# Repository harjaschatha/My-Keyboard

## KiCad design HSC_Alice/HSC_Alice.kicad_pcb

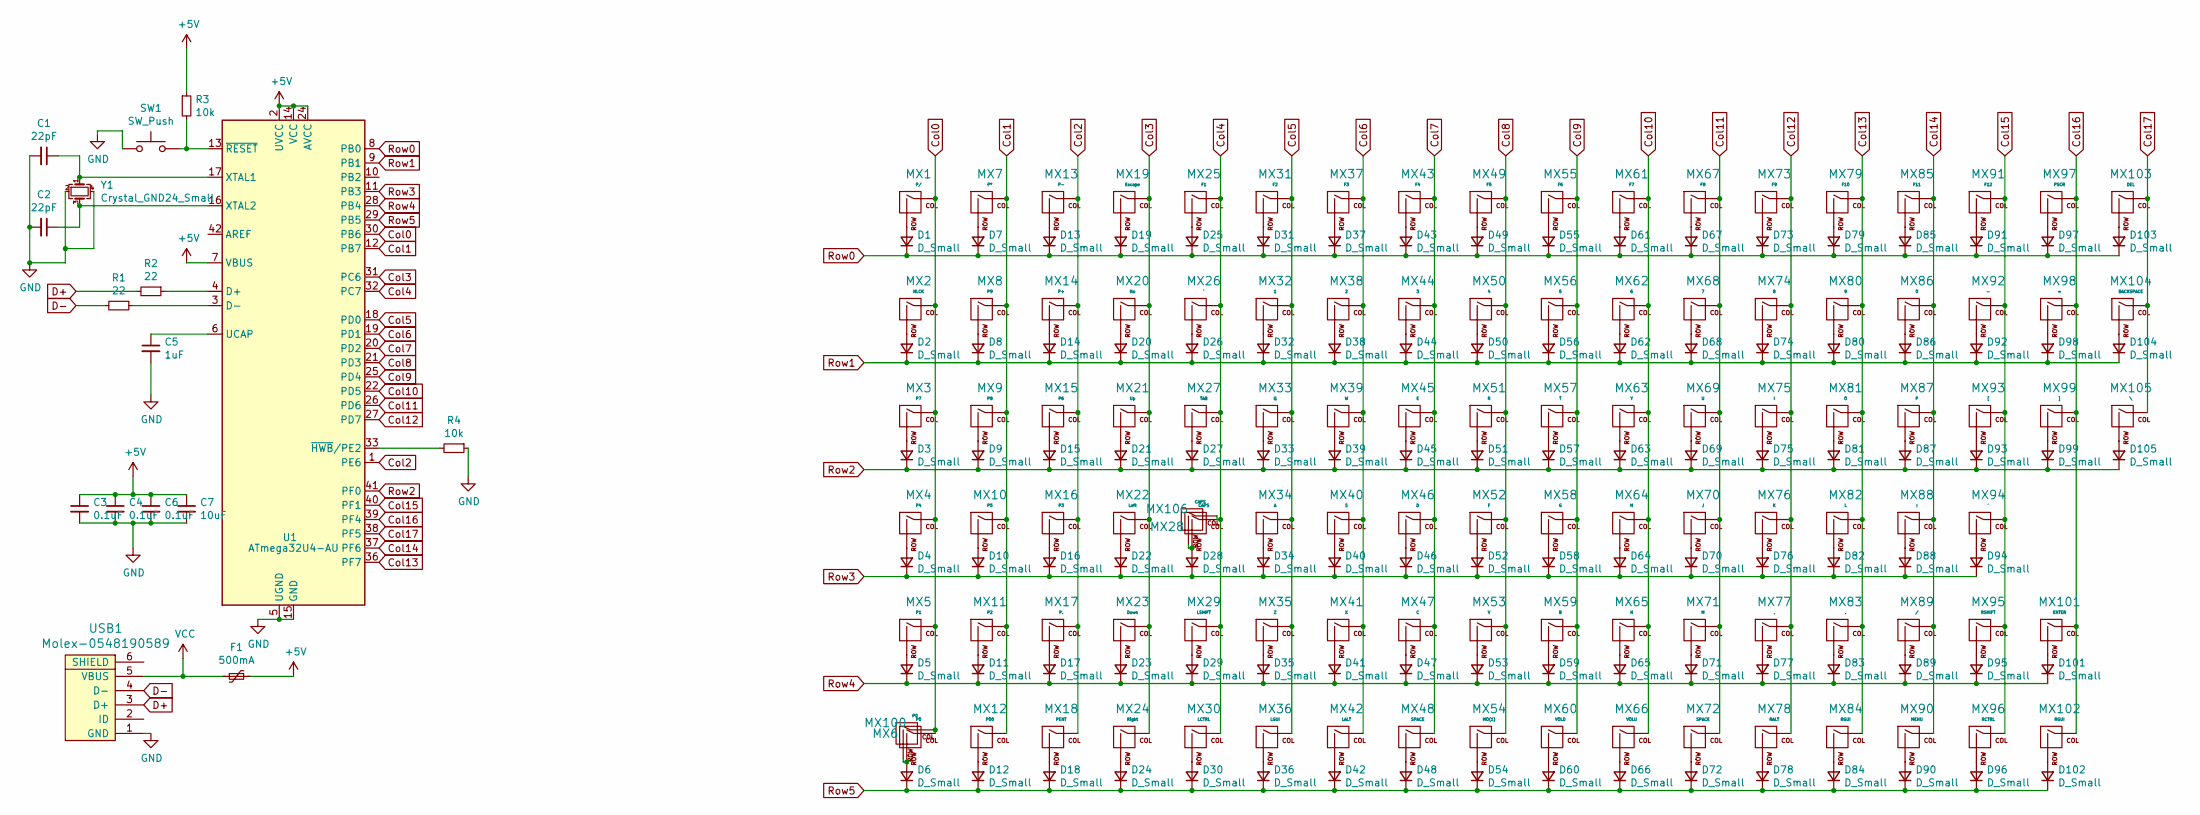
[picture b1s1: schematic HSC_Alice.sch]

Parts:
C1, C2: 22pF; C_0805_2012Metric
C3, C4, C6: 0.1uF; C_0805_2012Metric
C5: 1uF; C_0805_2012Metric
C7: 10uF; C_0805_2012Metric
D1, D2, D3, D4, D5, D6, D7, D8, D9, D10, D11, D12, D13, D14, D15, D16, D17, D18, D19, D20, D21, D22, D23, D24, D25, D26, D27, D28, D29, D30, D31, D32, D33, D34, D35, D36, D37, D38, D39, D40, D41, D42, D43, D44, D45, D46, D47, D48, D49, D50, D51, D52, D53, D54, D55, D56, D57, D58, D59, D60, D61, D62, D63, D64, D65, D66, D67, D68, D69, D70, D71, D72, D73, D74, D75, D76, D77, D78, D79, D80, D81, D82, D83, D84, D85, D86, D87, D88, D89, D90, D91, D92, D93, D94, D95, D96, D97, D98, D99, D101, D102, D103, D104, D105: D_Small; D_SOD-123
F1: 500mA; Fuse_1206_3216Metric
MX1: P/; MXOnly-1U-Hotswap
MX2: NLCK; MXOnly-1U-Hotswap
MX3: P7; MXOnly-1U-Hotswap
MX4: P4; MXOnly-1U-Hotswap
MX5: P1; MXOnly-1U-Hotswap
MX6: P0; MXOnly-1U-Hotswap
MX7: P*; MXOnly-1U-Hotswap
MX8: P9; MXOnly-1U-Hotswap
MX9: P8; MXOnly-1U-Hotswap
MX10: P5; MXOnly-1U-Hotswap
MX11: P2; MXOnly-1U-Hotswap
MX12: P00; MXOnly-1U-Hotswap
MX13: P-; MXOnly-1U-Hotswap
MX14: P+; MXOnly-2U-Hotswap
MX15: P6; MXOnly-1U-Hotswap
MX16: P3; MXOnly-1U-Hotswap
MX17: P.; MXOnly-1U-Hotswap
MX18: PENT; MXOnly-2U-Hotswap
MX19: Escape; MXOnly-1U-Hotswap
MX20: No; MXOnly-1U-Hotswap
MX21: Up; MXOnly-1U-Hotswap
MX22: Left; MXOnly-1U-Hotswap
MX23: Down; MXOnly-1U-Hotswap
MX24: Right; MXOnly-1U-Hotswap
MX25: F1; MXOnly-1U-Hotswap
MX26: `; MXOnly-1U-Hotswap
MX27: TAB; MXOnly-1.5U-Hotswap
MX28: CAPS; MXOnly-1.75U-Hotswap
MX29: LSHIFT; MXOnly-2.25U-Hotswap
MX30: LCTRL; MXOnly-1.25U-Hotswap
MX31: F2; MXOnly-1U-Hotswap
MX32: 1; MXOnly-1U-Hotswap
MX33: Q; MXOnly-1U-Hotswap
MX34: A; MXOnly-1U-Hotswap
MX35: Z; MXOnly-1U-Hotswap
MX36: LGUI; MXOnly-1.25U-Hotswap
MX37: F3; MXOnly-1U-Hotswap
MX38: 2; MXOnly-1U-Hotswap
MX39: W; MXOnly-1U-Hotswap
MX40: S; MXOnly-1U-Hotswap
MX41: X; MXOnly-1U-Hotswap
MX42: LALT; MXOnly-1.25U-Hotswap
MX43: F4; MXOnly-1U-Hotswap
MX44: 3; MXOnly-1U-Hotswap
MX45: E; MXOnly-1U-Hotswap
MX46: D; MXOnly-1U-Hotswap
MX47: C; MXOnly-1U-Hotswap
MX48, MX72: SPACE; MXOnly-2.75U-Hotswap-ReversedStabilizers
MX49: F5; MXOnly-1U-Hotswap
MX50: 4; MXOnly-1U-Hotswap
MX51: R; MXOnly-1U-Hotswap
MX52: F; MXOnly-1U-Hotswap
MX53: V; MXOnly-1U-Hotswap
MX54: MO(1); MXOnly-1U-Hotswap
MX55: F6; MXOnly-1U-Hotswap
MX56: 5; MXOnly-1U-Hotswap
MX57: T; MXOnly-1U-Hotswap
MX58: G; MXOnly-1U-Hotswap
MX59: B; MXOnly-1U-Hotswap
MX60: VOLD; MXOnly-1U-Hotswap
MX61: F7; MXOnly-1U-Hotswap
MX62: 6; MXOnly-1U-Hotswap
MX63: Y; MXOnly-1U-Hotswap
MX64: H; MXOnly-1U-Hotswap
MX65: N; MXOnly-1U-Hotswap
MX66: VOLU; MXOnly-1U-Hotswap
MX67: F8; MXOnly-1U-Hotswap
MX68: 7; MXOnly-1U-Hotswap
MX69: U; MXOnly-1U-Hotswap
MX70: J; MXOnly-1U-Hotswap
MX71: M; MXOnly-1U-Hotswap
MX73: F9; MXOnly-1U-Hotswap
MX74: 8; MXOnly-1U-Hotswap
MX75: I; MXOnly-1U-Hotswap
MX76: K; MXOnly-1U-Hotswap
MX77: ,; MXOnly-1U-Hotswap
MX78: RALT; MXOnly-1.25U-Hotswap
MX79: F10; MXOnly-1U-Hotswap
MX80: 9; MXOnly-1U-Hotswap
MX81: O; MXOnly-1U-Hotswap
MX82: L; MXOnly-1U-Hotswap
MX83: .; MXOnly-1U-Hotswap
MX84: RGUI; MXOnly-1.25U-Hotswap
MX85: F11; MXOnly-1U-Hotswap
MX86: 0; MXOnly-1U-Hotswap
MX87: P; MXOnly-1U-Hotswap
MX88: ;; MXOnly-1U-Hotswap
MX89: /; MXOnly-1U-Hotswap
MX90: MENU; MXOnly-1.25U-Hotswap
MX91: F12; MXOnly-1U-Hotswap
MX92: -; MXOnly-1U-Hotswap
MX93: [; MXOnly-1U-Hotswap
MX94: '; MXOnly-1U-Hotswap
MX95: RSHIFT; MXOnly-2.25U-Hotswap
MX96: RCTRL; MXOnly-1.25U-Hotswap
MX97: PSCR; MXOnly-1U-Hotswap
MX98: =; MXOnly-1U-Hotswap
MX99: ]; MXOnly-1U-Hotswap
MX100: P0; MXOnly-2U-Hotswap-ReversedStabilizers
MX101: ENTER; MXOnly-2.25U-Hotswap
MX102: RGUI; MXOnly-1U-Hotswap
MX103: DEL; MXOnly-1U-Hotswap
MX104: BACKSPACE; MXOnly-2U-Hotswap
MX105: \\; MXOnly-1.5U-Hotswap
MX106: CAPS; MXOnly-1.25U-Hotswap
R1, R2: 22; R_0805_2012Metric
R3, R4: 10k; R_0805_2012Metric
SW1: SW_Push; SKQG-1155865
U1: ATmega32U4-AU; TQFP-44_10x10mm_P0.8mm
USB1: Molex-0548190589
Y1: Crystal_GND24_Small; Crystal_SMD_3225-4Pin_3.2x2.5mm

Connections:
+5V: C3.1, C4.1, C6.1, C7.1, F1.1, R3.1, U1.2 (UVCC), U1.7 (VBUS), U1.14 (VCC), U1.24 (AVCC), U1.34 (VCC), U1.44 (AVCC)
Col0: MX1.1 (COL), MX2.1 (COL), MX3.1 (COL), MX4.1 (COL), MX5.1 (COL), MX6.1 (COL), MX100.1 (COL), U1.30 (PB6)
Col1: MX7.1 (COL), MX8.1 (COL), MX9.1 (COL), MX10.1 (COL), MX11.1 (COL), MX12.1 (COL), U1.12 (PB7)
Col2: MX13.1 (COL), MX14.1 (COL), MX15.1 (COL), MX16.1 (COL), MX17.1 (COL), MX18.1 (COL), U1.1 (PE6)
Col3: MX19.1 (COL), MX20.1 (COL), MX21.1 (COL), MX22.1 (COL), MX23.1 (COL), MX24.1 (COL), U1.31 (PC6)
Col4: MX25.1 (COL), MX26.1 (COL), MX27.1 (COL), MX28.1 (COL), MX29.1 (COL), MX30.1 (COL), MX106.1 (COL), U1.32 (PC7)
Col5: MX31.1 (COL), MX32.1 (COL), MX33.1 (COL), MX34.1 (COL), MX35.1 (COL), MX36.1 (COL), U1.18 (PD0)
Col6: MX37.1 (COL), MX38.1 (COL), MX39.1 (COL), MX40.1 (COL), MX41.1 (COL), MX42.1 (COL), U1.19 (PD1)
Col7: MX43.1 (COL), MX44.1 (COL), MX45.1 (COL), MX46.1 (COL), MX47.1 (COL), MX48.1 (COL), U1.20 (PD2)
Col8: MX49.1 (COL), MX50.1 (COL), MX51.1 (COL), MX52.1 (COL), MX53.1 (COL), MX54.1 (COL), U1.21 (PD3)
Col9: MX55.1 (COL), MX56.1 (COL), MX57.1 (COL), MX58.1 (COL), MX59.1 (COL), MX60.1 (COL), U1.25 (PD4)
Col10: MX61.1 (COL), MX62.1 (COL), MX63.1 (COL), MX64.1 (COL), MX65.1 (COL), MX66.1 (COL), U1.22 (PD5)
Col11: MX67.1 (COL), MX68.1 (COL), MX69.1 (COL), MX70.1 (COL), MX71.1 (COL), MX72.1 (COL), U1.26 (PD6)
Col12: MX73.1 (COL), MX74.1 (COL), MX75.1 (COL), MX76.1 (COL), MX77.1 (COL), MX78.1 (COL), U1.27 (PD7)
Col13: MX79.1 (COL), MX80.1 (COL), MX81.1 (COL), MX82.1 (COL), MX83.1 (COL), MX84.1 (COL), U1.36 (PF7)
Col14: MX85.1 (COL), MX86.1 (COL), MX87.1 (COL), MX88.1 (COL), MX89.1 (COL), MX90.1 (COL), U1.37 (PF6)
Col15: MX91.1 (COL), MX92.1 (COL), MX93.1 (COL), MX94.1 (COL), MX95.1 (COL), MX96.1 (COL), U1.40 (PF1)
Col16: MX97.1 (COL), MX98.1 (COL), MX99.1 (COL), MX101.1 (COL), MX102.1 (COL), U1.39 (PF4)
Col17: MX103.1 (COL), MX104.1 (COL), MX105.1 (COL), U1.38 (PF5)
D+: R2.2, USB1.3 (D+)
D-: R1.2, USB1.4 (D-)
GND: C1.2, C2.2, C3.2, C4.2, C5.2, C6.2, C7.2, R4.1, SW1.1, U1.5 (UGND), U1.15 (GND), U1.23 (GND), U1.35 (GND), U1.43 (GND), USB1.1 (GND), Y1.2, Y1.4
unnamed: C1.1, U1.17 (XTAL1), Y1.1
unnamed: C2.1, U1.16 (XTAL2), Y1.3
unnamed: C5.1, U1.6 (UCAP)
unnamed: D1.2 (A), MX1.2 (ROW)
unnamed: D2.2 (A), MX2.2 (ROW)
unnamed: D3.2 (A), MX3.2 (ROW)
unnamed: D4.2 (A), MX4.2 (ROW)
unnamed: D5.2 (A), MX5.2 (ROW)
unnamed: D6.2 (A), MX6.2 (ROW), MX100.2 (ROW)
unnamed: D7.2 (A), MX7.2 (ROW)
unnamed: D8.2 (A), MX8.2 (ROW)
unnamed: D9.2 (A), MX9.2 (ROW)
unnamed: D10.2 (A), MX10.2 (ROW)
unnamed: D11.2 (A), MX11.2 (ROW)
unnamed: D12.2 (A), MX12.2 (ROW)
unnamed: D13.2 (A), MX13.2 (ROW)
unnamed: D14.2 (A), MX14.2 (ROW)
unnamed: D15.2 (A), MX15.2 (ROW)
unnamed: D16.2 (A), MX16.2 (ROW)
unnamed: D17.2 (A), MX17.2 (ROW)
unnamed: D18.2 (A), MX18.2 (ROW)
unnamed: D19.2 (A), MX19.2 (ROW)
unnamed: D20.2 (A), MX20.2 (ROW)
unnamed: D21.2 (A), MX21.2 (ROW)
unnamed: D22.2 (A), MX22.2 (ROW)
unnamed: D23.2 (A), MX23.2 (ROW)
unnamed: D24.2 (A), MX24.2 (ROW)
unnamed: D25.2 (A), MX25.2 (ROW)
unnamed: D26.2 (A), MX26.2 (ROW)
unnamed: D27.2 (A), MX27.2 (ROW)
unnamed: D28.2 (A), MX28.2 (ROW), MX106.2 (ROW)
unnamed: D29.2 (A), MX29.2 (ROW)
unnamed: D30.2 (A), MX30.2 (ROW)
unnamed: D31.2 (A), MX31.2 (ROW)
unnamed: D32.2 (A), MX32.2 (ROW)
unnamed: D33.2 (A), MX33.2 (ROW)
unnamed: D34.2 (A), MX34.2 (ROW)
unnamed: D35.2 (A), MX35.2 (ROW)
unnamed: D36.2 (A), MX36.2 (ROW)
unnamed: D37.2 (A), MX37.2 (ROW)
unnamed: D38.2 (A), MX38.2 (ROW)
unnamed: D39.2 (A), MX39.2 (ROW)
unnamed: D40.2 (A), MX40.2 (ROW)
unnamed: D41.2 (A), MX41.2 (ROW)
unnamed: D42.2 (A), MX42.2 (ROW)
unnamed: D43.2 (A), MX43.2 (ROW)
unnamed: D44.2 (A), MX44.2 (ROW)
unnamed: D45.2 (A), MX45.2 (ROW)
unnamed: D46.2 (A), MX46.2 (ROW)
unnamed: D47.2 (A), MX47.2 (ROW)
unnamed: D48.2 (A), MX48.2 (ROW)
unnamed: D49.2 (A), MX49.2 (ROW)
unnamed: D50.2 (A), MX50.2 (ROW)
unnamed: D51.2 (A), MX51.2 (ROW)
unnamed: D52.2 (A), MX52.2 (ROW)
unnamed: D53.2 (A), MX53.2 (ROW)
unnamed: D54.2 (A), MX54.2 (ROW)
unnamed: D55.2 (A), MX55.2 (ROW)
unnamed: D56.2 (A), MX56.2 (ROW)
unnamed: D57.2 (A), MX57.2 (ROW)
unnamed: D58.2 (A), MX58.2 (ROW)
unnamed: D59.2 (A), MX59.2 (ROW)
unnamed: D60.2 (A), MX60.2 (ROW)
unnamed: D61.2 (A), MX61.2 (ROW)
unnamed: D62.2 (A), MX62.2 (ROW)
unnamed: D63.2 (A), MX63.2 (ROW)
unnamed: D64.2 (A), MX64.2 (ROW)
unnamed: D65.2 (A), MX65.2 (ROW)
unnamed: D66.2 (A), MX66.2 (ROW)
unnamed: D67.2 (A), MX67.2 (ROW)
unnamed: D68.2 (A), MX68.2 (ROW)
unnamed: D69.2 (A), MX69.2 (ROW)
unnamed: D70.2 (A), MX70.2 (ROW)
unnamed: D71.2 (A), MX71.2 (ROW)
unnamed: D72.2 (A), MX72.2 (ROW)
unnamed: D73.2 (A), MX73.2 (ROW)
unnamed: D74.2 (A), MX74.2 (ROW)
unnamed: D75.2 (A), MX75.2 (ROW)
unnamed: D76.2 (A), MX76.2 (ROW)
unnamed: D77.2 (A), MX77.2 (ROW)
unnamed: D78.2 (A), MX78.2 (ROW)
unnamed: D79.2 (A), MX79.2 (ROW)
unnamed: D80.2 (A), MX80.2 (ROW)
unnamed: D81.2 (A), MX81.2 (ROW)
unnamed: D82.2 (A), MX82.2 (ROW)
unnamed: D83.2 (A), MX83.2 (ROW)
unnamed: D84.2 (A), MX84.2 (ROW)
unnamed: D85.2 (A), MX85.2 (ROW)
unnamed: D86.2 (A), MX86.2 (ROW)
unnamed: D87.2 (A), MX87.2 (ROW)
unnamed: D88.2 (A), MX88.2 (ROW)
unnamed: D89.2 (A), MX89.2 (ROW)
unnamed: D90.2 (A), MX90.2 (ROW)
unnamed: D91.2 (A), MX91.2 (ROW)
unnamed: D92.2 (A), MX92.2 (ROW)
unnamed: D93.2 (A), MX93.2 (ROW)
unnamed: D94.2 (A), MX94.2 (ROW)
unnamed: D95.2 (A), MX95.2 (ROW)
unnamed: D96.2 (A), MX96.2 (ROW)
unnamed: D97.2 (A), MX97.2 (ROW)
unnamed: D98.2 (A), MX98.2 (ROW)
unnamed: D99.2 (A), MX99.2 (ROW)
unnamed: D101.2 (A), MX101.2 (ROW)
unnamed: D102.2 (A), MX102.2 (ROW)
unnamed: D103.2 (A), MX103.2 (ROW)
unnamed: D104.2 (A), MX104.2 (ROW)
unnamed: D105.2 (A), MX105.2 (ROW)
unnamed: R1.1, U1.3 (D-)
unnamed: R2.1, U1.4 (D+)
unnamed: R3.2, SW1.2, U1.13 (~RESET)
unnamed: R4.2, U1.33 (~HWB~/PE2)
Row0: D1.1 (K), D7.1 (K), D13.1 (K), D19.1 (K), D25.1 (K), D31.1 (K), D37.1 (K), D43.1 (K), D49.1 (K), D55.1 (K), D61.1 (K), D67.1 (K), D73.1 (K), D79.1 (K), D85.1 (K), D91.1 (K), D97.1 (K), D103.1 (K), U1.8 (PB0)
Row1: D2.1 (K), D8.1 (K), D14.1 (K), D20.1 (K), D26.1 (K), D32.1 (K), D38.1 (K), D44.1 (K), D50.1 (K), D56.1 (K), D62.1 (K), D68.1 (K), D74.1 (K), D80.1 (K), D86.1 (K), D92.1 (K), D98.1 (K), D104.1 (K), U1.9 (PB1)
Row2: D3.1 (K), D9.1 (K), D15.1 (K), D21.1 (K), D27.1 (K), D33.1 (K), D39.1 (K), D45.1 (K), D51.1 (K), D57.1 (K), D63.1 (K), D69.1 (K), D75.1 (K), D81.1 (K), D87.1 (K), D93.1 (K), D99.1 (K), D105.1 (K), U1.41 (PF0)
Row3: D4.1 (K), D10.1 (K), D16.1 (K), D22.1 (K), D28.1 (K), D34.1 (K), D40.1 (K), D46.1 (K), D52.1 (K), D58.1 (K), D64.1 (K), D70.1 (K), D76.1 (K), D82.1 (K), D88.1 (K), D94.1 (K), U1.11 (PB3)
Row4: D5.1 (K), D11.1 (K), D17.1 (K), D23.1 (K), D29.1 (K), D35.1 (K), D41.1 (K), D47.1 (K), D53.1 (K), D59.1 (K), D65.1 (K), D71.1 (K), D77.1 (K), D83.1 (K), D89.1 (K), D95.1 (K), D101.1 (K), U1.28 (PB4)
Row5: D6.1 (K), D12.1 (K), D18.1 (K), D24.1 (K), D30.1 (K), D36.1 (K), D42.1 (K), D48.1 (K), D54.1 (K), D60.1 (K), D66.1 (K), D72.1 (K), D78.1 (K), D84.1 (K), D90.1 (K), D96.1 (K), D102.1 (K), U1.29 (PB5)
VCC: F1.2, USB1.5 (VBUS)

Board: 2 copper layers, 226 parts (120 on the bottom side), 140 nets, no tracks yet.

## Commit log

2021-06-17 Set up Schematic
    Added Schematic and inserted Microcontroller and USB connection
2021-06-17 Added Symbol Library
    Added Symbol library from Shark50 project file
2021-06-17 Removed faulty Acheron and Shark Library
2021-06-17 Add submodules
2021-06-17 Update sym-lib-table
    Added Footprint and Symbol library
2021-06-18 Add USB C connector
2021-06-18 SQ1 Set up Schematic
    Added Footprints and symbols for all components except USB
2021-06-18 PCB
    Added PCB and initial routing
2021-06-18 Add submodules for Elite-C
2021-06-18 Add submodules for Kicad Library of keebio
2021-06-19 Add Switches and Elite C
2021-06-19 Numpad
    Added Numpad Row and Col
2021-06-19 1st angled col added
2021-06-19 Aligned Left side and Flip Diodes
    Deleted traces
    Placed Diodes on back side of board
2021-06-20 Finished PCB
2021-06-20 Microcontroller
2021-06-20 Bug Fixes
    Fixed wiring 90Deg angles
    Reworked Gerber Files
2021-06-20 Update HSC_Alice.kicad_pcb
    Fixed routing errors
2021-06-21 Plate File
2021-06-21 PCB Plate
2021-06-21 AutoCad Plate Design
2021-06-22 Minor Fixes
    Update Plate design
2021-06-22 Bug Fixes
    Alignment, footprints and placement fixed
2021-06-22 Update fp-info-cache
2021-06-22 Removed Tracks
    Rework tracks
2021-06-24 Re-haul Schematics
    Placed all SMD components on backside of PCB
2021-06-24 Gerber Printed
2021-06-26 Layout edit
2021-06-26 Removed extra from schematic
2021-06-27 Fixed Orientation of Switches
2021-06-28 Plotted plate files
2021-06-29 Edited PCB and Plate
2021-07-04 Updated Gerber, BOM and POS files
2021-07-04 Fixed exporting files for plate
2021-07-08 Added Keebio components
2021-07-08 Revert "Removed extra from schematic"
    This reverts commit 69982eab7aea7fecda55a90420993644e7f6a179.
2021-07-08 Update PCB with Hot Swap sockets
